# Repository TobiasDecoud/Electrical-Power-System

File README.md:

# Electrical-Power-Subsystem

Necesitamos:
 
  Potencia Requerida: Estimar el consumo de energía promedio y pico de todos los subsistemas del satélite.
  
  Órbita del Satélite: Determinar los períodos de luz solar y eclipse para dimensionar los paneles solares y la capacidad de las baterías.
  
  Vida Útil: Seleccionar componentes que puedan soportar la duración de la misión y los ciclos de carga y descarga.

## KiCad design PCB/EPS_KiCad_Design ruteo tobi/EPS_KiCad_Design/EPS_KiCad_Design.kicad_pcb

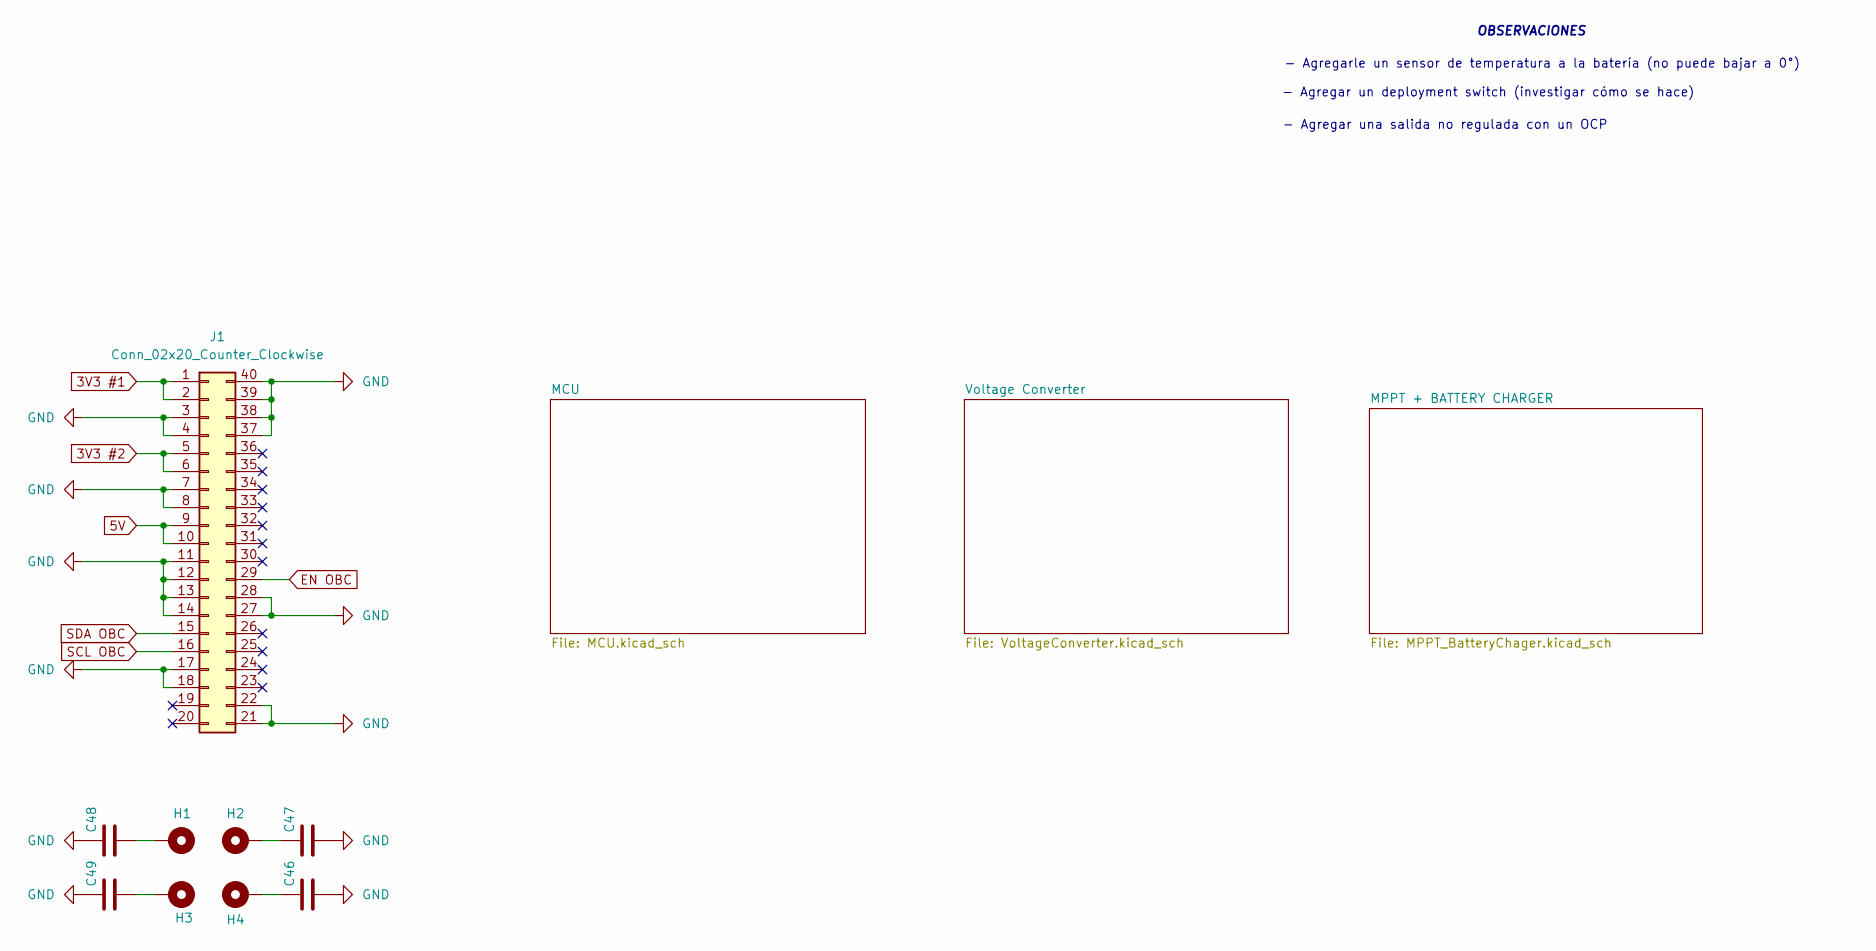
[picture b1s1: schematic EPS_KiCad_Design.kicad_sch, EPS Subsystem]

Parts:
C46, C47, C48, C49: 100nF; C_0805_2012Metric_Pad1.18x1.45mm_HandSolder
H1, H2, H3, H4: MountingHole_Pad; MountingHole_3.2mm_M3_Pad_Via
J1: Conn_02x20_Counter_Clockwise; PinSocket_2x20_P2.54mm_Vertical

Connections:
3V3 #1: J1.1, J1.2; also elsewhere on the board
3V3 #2: J1.5, J1.6; also elsewhere on the board
5V: J1.9, J1.10; also elsewhere on the board
EN OBC: J1.29; also elsewhere on the board
GND: C46.2, C47.2, C48.1, C49.1, J1.3, J1.4, J1.7, J1.8, J1.11, J1.12, J1.13, J1.14, J1.17, J1.18, J1.21, J1.22, J1.27, J1.28, J1.37, J1.38, J1.39, J1.40; also elsewhere on the board
unnamed: C46.1, H4.1
unnamed: C47.1, H2.1
unnamed: C48.2, H1.1
unnamed: C49.2, H3.1
SCL OBC: J1.16; also elsewhere on the board
SDA OBC: J1.15; also elsewhere on the board

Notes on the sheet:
OBSERVACIONES
- Agregar un deployment switch (investigar cómo se hace)
- Agregarle un sensor de temperatura a la batería (no puede bajar a 0°)
- Agregar una salida no regulada con un OCP

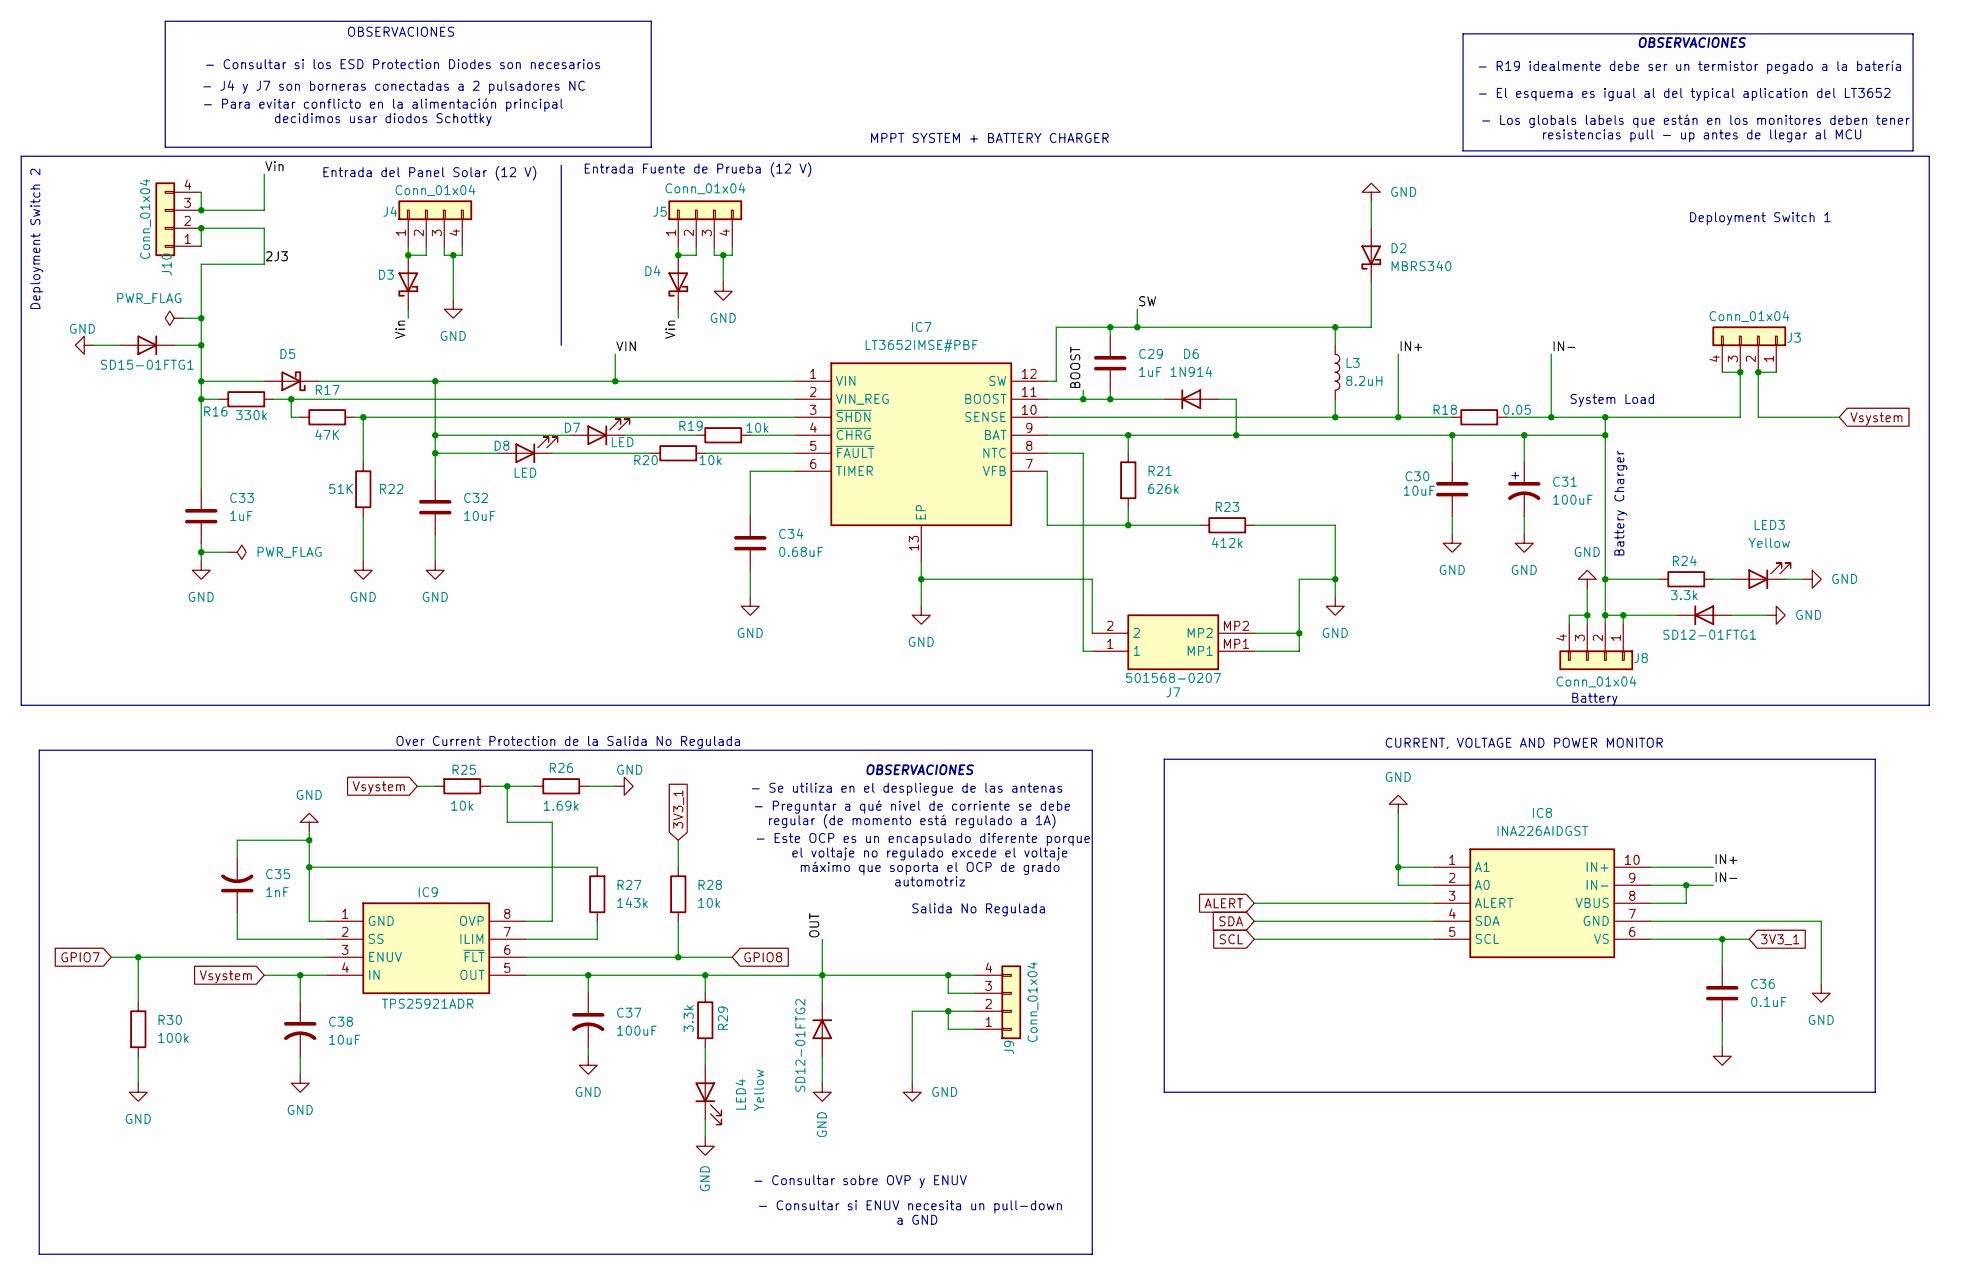
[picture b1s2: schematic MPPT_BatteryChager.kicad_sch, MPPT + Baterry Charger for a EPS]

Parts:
C29, C33: 1uF; C_0805_2012Metric_Pad1.18x1.45mm_HandSolder
C30, C32, C38: 10uF; C_0805_2012Metric_Pad1.18x1.45mm_HandSolder
C31, C37: 100uF; CAPPM7344X310N
C34: 0.68uF; C_0805_2012Metric_Pad1.18x1.45mm_HandSolder
C35: 1nF; C_0805_2012Metric_Pad1.18x1.45mm_HandSolder
C36: 0.1uF; C_0805_2012Metric_Pad1.18x1.45mm_HandSolder
D2, D3, D4, D5: MBRS340; SODFL3517X110N
D6: 1N914; SODFL4725X110N
D7, D8: LED; LED_0805_2012Metric_Pad1.15x1.40mm_HandSolder
IC7: LT3652IMSE#PBF; SOP65P490X110-13N; Mouser Part Number 584-LT3652IMSE#PBF
IC8: INA226AIDGST; SOP50P490X110-10N; Mouser Part Number 595-INA226AIDGST
IC9: TPS25921ADR; SOIC127P600X175-8N; Mouser Part Number 595-TPS25921ADR
J3, J4, J5, J8, J9, J10: Conn_01x04; 62000411722
J7: 501568-0207; 5015680207; Mouser Part Number 538-501568-0207
L3: 8.2uH; INDPM7168X300N
LED3, LED4: Yellow; LED_0805_2012Metric_Pad1.15x1.40mm_HandSolder
R16: 330k; R_0805_2012Metric_Pad1.20x1.40mm_HandSolder
R17: 47K; R_0805_2012Metric_Pad1.20x1.40mm_HandSolder
R18: 0.05; R_0805_2012Metric_Pad1.20x1.40mm_HandSolder
R19, R20, R25, R28: 10k; R_0805_2012Metric_Pad1.20x1.40mm_HandSolder
R21: 626k; R_0805_2012Metric_Pad1.20x1.40mm_HandSolder
R22: 51K; R_0805_2012Metric_Pad1.20x1.40mm_HandSolder
R23: 412k; R_0805_2012Metric_Pad1.20x1.40mm_HandSolder
R24, R29: 3.3k; R_0805_2012Metric_Pad1.20x1.40mm_HandSolder
R26: 1.69k; R_0805_2012Metric_Pad1.20x1.40mm_HandSolder
R27: 143k; R_0805_2012Metric_Pad1.20x1.40mm_HandSolder
R30: 100k; R_0805_2012Metric_Pad1.20x1.40mm_HandSolder
SD12-01FTG1, SD12-01FTG2: SOD2613X114N
SD15-01FTG1: D; SOD2613X114N

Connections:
3V3_1: C36.1, IC8.6 (VS), R28.1; also elsewhere on the board
/MPPT + BATTERY CHARGER/2J3: C33.1, D5.2 (A), J10.1, J10.2, R16.1, SD15-01FTG1.1 (K)
/MPPT + BATTERY CHARGER/BOOST: C29.2, D6.1 (K), IC7.11 (BOOST)
/MPPT + BATTERY CHARGER/IN+: IC7.10 (SENSE), IC8.10 (IN+), L3.2, R18.1
/MPPT + BATTERY CHARGER/IN-: C30.1, C31.1, D6.2 (A), IC7.9 (BAT), IC8.8 (VBUS), IC8.9 (IN-), J3.3, J3.4, J8.1, J8.2, R18.2, R21.1, R24.1, SD12-01FTG1.1 (K)
/MPPT + BATTERY CHARGER/OUT: C37.1, IC9.5 (OUT), J9.3, J9.4, R29.1, SD12-01FTG2.1 (K)
/MPPT + BATTERY CHARGER/SW: C29.1, D2.1 (K), IC7.12 (SW), L3.1
/MPPT + BATTERY CHARGER/VIN: C32.1, D5.1 (K), D7.2 (A), D8.2 (A), IC7.1 (VIN)
/MPPT + BATTERY CHARGER/Vin: D3.1 (K), D4.1 (K), J10.3, J10.4
ALERT: IC8.3 (ALERT); also elsewhere on the board
GND: C30.2, C31.2, C32.2, C33.2, C34.2, C35.2, C36.2, C37.2, C38.2, D2.2 (A), IC7.13 (EP), IC8.1 (A1), IC8.2 (A0), IC8.7 (GND), IC9.1 (GND), J4.3, J4.4, J5.3, J5.4, J7.2, J7.MP1, J7.MP2, J8.3, J8.4, J9.1, J9.2, LED3.1 (K), LED4.1 (K), R22.2, R23.2, R26.2, R27.2, R30.2, SD12-01FTG1.2 (A), SD12-01FTG2.2 (A), SD15-01FTG1.2 (A); also elsewhere on the board
GPIO7: IC9.3 (ENUV), R30.1; also elsewhere on the board
GPIO8: IC9.6 (~FLT), R28.2; also elsewhere on the board
unnamed: D3.2 (A), J4.1, J4.2
unnamed: D4.2 (A), J5.1, J5.2
unnamed: D7.1 (K), R19.1
unnamed: D8.1 (K), R20.1
unnamed: IC7.8 (NTC), J7.1
unnamed: C34.1, IC7.6 (TIMER)
unnamed: IC7.7 (VFB), R21.2, R23.1
unnamed: IC7.2 (VIN_REG), R16.2, R17.1
unnamed: IC7.4 (~CHRG), R19.2
unnamed: IC7.5 (~FAULT), R20.2
unnamed: IC7.3 (~SHDN), R17.2, R22.1
unnamed: IC9.7 (ILIM), R27.1
unnamed: IC9.8 (OVP), R25.1, R26.1
unnamed: C35.1, IC9.2 (SS)
unnamed: LED3.2 (A), R24.2
unnamed: LED4.2 (A), R29.2
SCL: IC8.5 (SCL); also elsewhere on the board
SDA: IC8.4 (SDA); also elsewhere on the board
Vsystem: C38.1, IC9.4 (IN), J3.1, J3.2, R25.2; also elsewhere on the board

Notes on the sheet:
CURRENT, VOLTAGE AND POWER MONITOR
- Se utiliza en el despliegue de las antenas
System Load
OBSERVACIONES
Entrada del Panel Solar (12 V)
- Los globals labels que están en los monitores deben tener resistencias pull - up antes de llegar al MCU
- Para evitar conflicto en la alimentación principal decidimos usar diodos Schottky
Battery Charger
- Este OCP es un encapsulado diferente porque el voltaje no regulado excede el voltaje máximo que soporta el OCP de grado automotriz
- El esquema es igual al del typical aplication del LT3652
Over Current Protection de la Salida No Regulada
- Consultar si ENUV necesita un pull-down a GND
Deployment Switch 1
Entrada Fuente de Prueba (12 V)
Deployment Switch 2
- R19 idealmente debe ser un termistor pegado a la batería
- J4 y J7 son borneras conectadas a 2 pulsadores NC
- Consultar si los ESD Protection Diodes son necesarios
- Consultar sobre OVP y ENUV
Salida No Regulada
- Preguntar a qué nivel de corriente se debe regular (de momento está regulado a 1A)
Battery
MPPT SYSTEM + BATTERY CHARGER

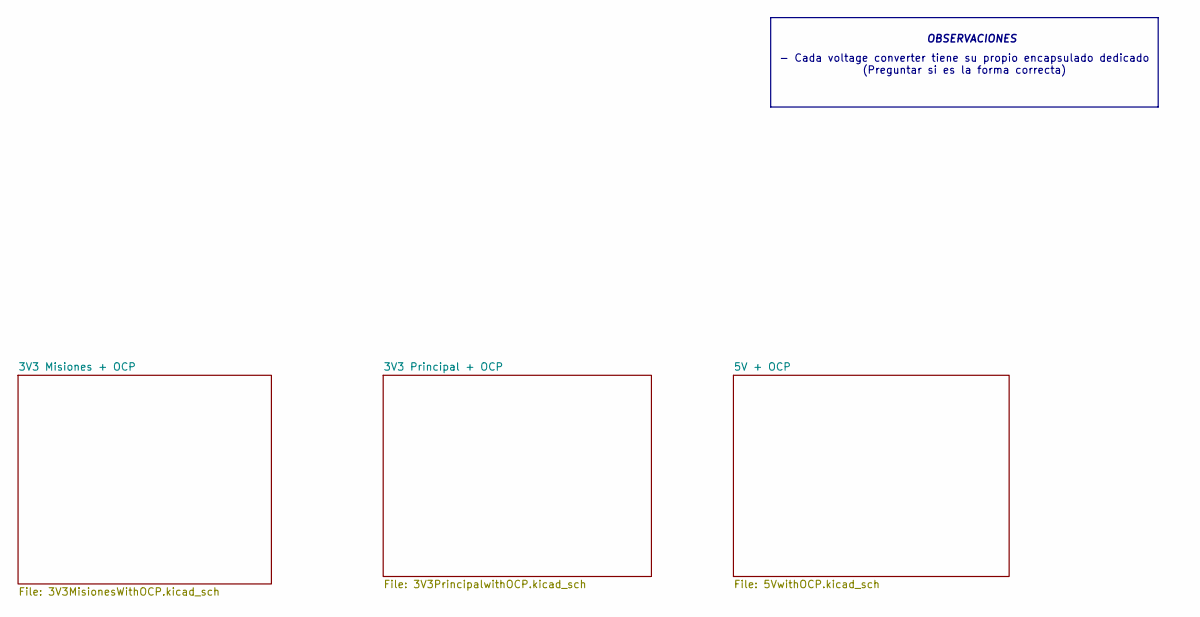
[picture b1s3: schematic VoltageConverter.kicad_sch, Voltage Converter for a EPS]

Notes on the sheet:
- Cada voltage converter tiene su propio encapsulado dedicado (Preguntar si es la forma correcta)
OBSERVACIONES

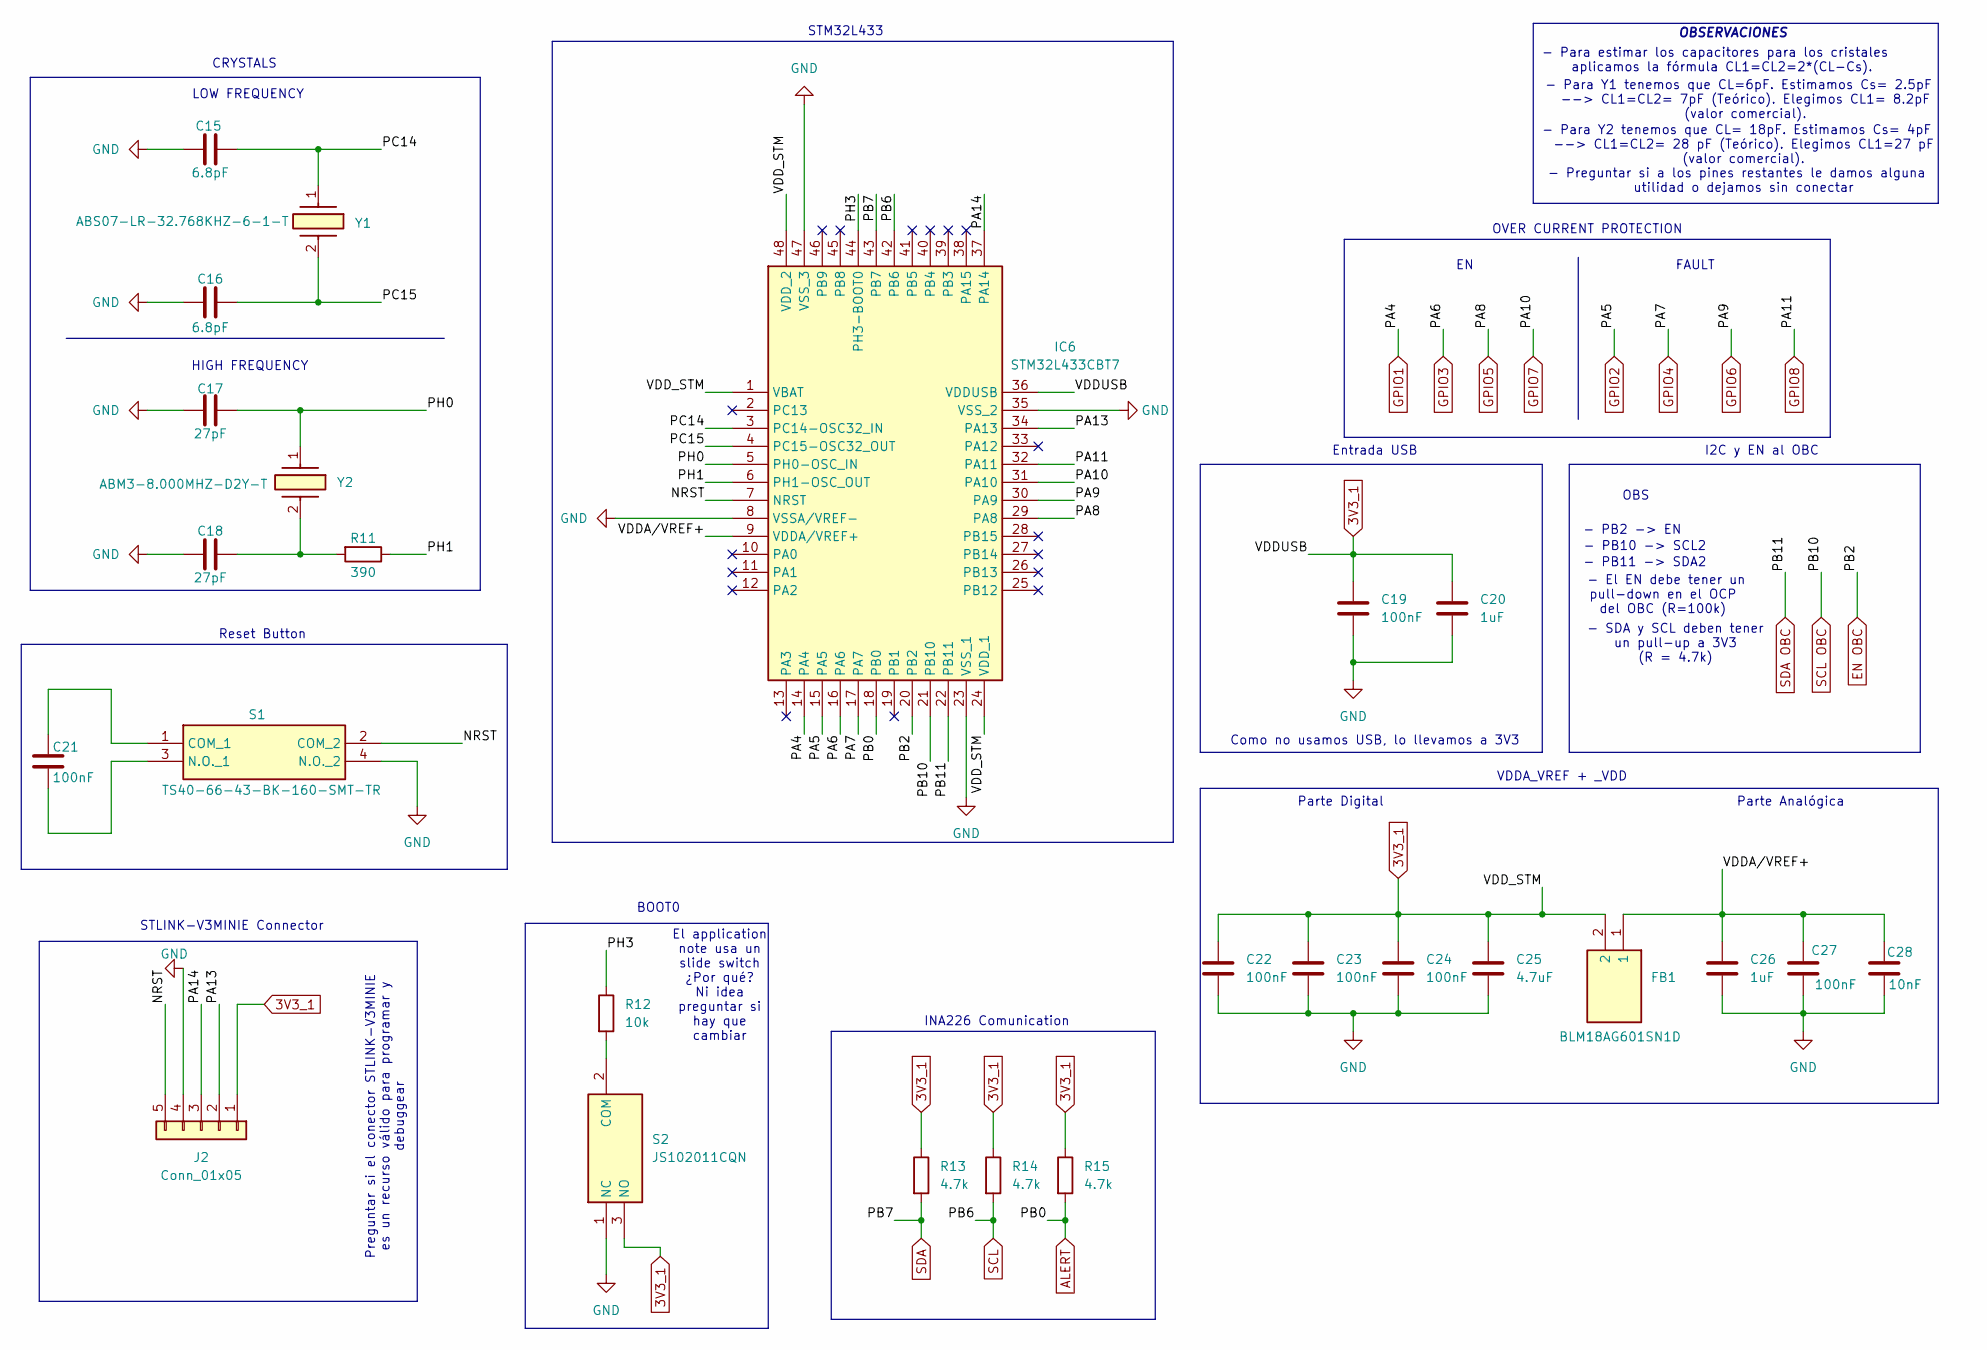
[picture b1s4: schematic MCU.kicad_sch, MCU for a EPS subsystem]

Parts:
C15, C16: 6.8pF; C_0805_2012Metric_Pad1.18x1.45mm_HandSolder
C17, C18: 27pF; C_0805_2012Metric_Pad1.18x1.45mm_HandSolder
C19, C21, C22, C23, C24, C27: 100nF; C_0805_2012Metric_Pad1.18x1.45mm_HandSolder
C20, C26: 1uF; C_0805_2012Metric_Pad1.18x1.45mm_HandSolder
C25: 4.7uF; C_0805_2012Metric_Pad1.18x1.45mm_HandSolder
C28: 10nF; C_0805_2012Metric_Pad1.18x1.45mm_HandSolder
FB1: BLM18AG601SN1D; BLM18SP221SN1B; Mouser Part Number 81-BLM11A601S
IC6: STM32L433CBT7; QFP50P900X900X160-48N; Mouser Part Number 511-STM32L433CBT7
J2: Conn_01x05; TSM10501LSV
R11: 390; R_0805_2012Metric_Pad1.20x1.40mm_HandSolder
R12: 10k; R_0805_2012Metric_Pad1.20x1.40mm_HandSolder
R13, R14, R15: 4.7k; R_0805_2012Metric_Pad1.20x1.40mm_HandSolder
S1: TS40-66-43-BK-160-SMT-TR; TS406643BK160SMTTR; Manufacturer_Part_Number TS40-66-43-BK-160-SMT-TR
S2: JS102011CQN; Mouser Part Number 611-JS102011CQN
Y1: ABS07-LR-32.768KHZ-6-1-T; ABS07LR32768kHz61T; Mouser Part Number 815-ABS07LR32.76-61T
Y2: ABM3-8.000MHZ-D2Y-T; ABM3; Mouser Part Number 815-ABM3-8-D2Y-T

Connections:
3V3_1: C19.1, C20.1, C22.1, C23.1, C24.1, C25.1, FB1.2, IC6.1 (VBAT), IC6.24 (VDD_1), IC6.36 (VDDUSB), IC6.48 (VDD_2), J2.1, R13.1, R14.1, R15.1, S2.3 (NO); also elsewhere on the board
/MCU/NRST: IC6.7 (NRST), J2.5, S1.2 (COM_2)
/MCU/PA13: IC6.34 (PA13), J2.2
/MCU/PA14: IC6.37 (PA14), J2.3
/MCU/PC14: C15.2, IC6.3 (PC14-OSC32_IN), Y1.1
/MCU/PC15: C16.2, IC6.4 (PC15-OSC32_OUT), Y1.2
/MCU/PH0: C17.1, IC6.5 (PH0-OSC_IN), Y2.1
/MCU/PH1: IC6.6 (PH1-OSC_OUT), R11.1
/MCU/PH3: IC6.44 (PH3-BOOT0), R12.1
/MCU/VDDA/VREF+: C26.1, C27.1, C28.1, FB1.1, IC6.9 (VDDA/VREF+)
ALERT: IC6.18 (PB0), R15.2; also elsewhere on the board
EN OBC: IC6.20 (PB2); also elsewhere on the board
GND: C15.1, C16.1, C17.2, C18.2, C19.2, C20.2, C22.2, C23.2, C24.2, C25.2, C26.2, C27.2, C28.2, IC6.8 (VSSA/VREF-), IC6.23 (VSS_1), IC6.35 (VSS_2), IC6.47 (VSS_3), J2.4, S1.4 (N.O._2), S2.1 (NC); also elsewhere on the board
GPIO1: IC6.14 (PA4); also elsewhere on the board
GPIO2: IC6.15 (PA5); also elsewhere on the board
GPIO3: IC6.16 (PA6); also elsewhere on the board
GPIO4: IC6.17 (PA7); also elsewhere on the board
GPIO5: IC6.29 (PA8); also elsewhere on the board
GPIO6: IC6.30 (PA9); also elsewhere on the board
GPIO7: IC6.31 (PA10); also elsewhere on the board
GPIO8: IC6.32 (PA11); also elsewhere on the board
unnamed: C18.1, R11.2, Y2.2
unnamed: C21.1, S1.1 (COM_1)
unnamed: C21.2, S1.3 (N.O._1)
unnamed: R12.2, S2.2 (COM)
SCL: IC6.42 (PB6), R14.2; also elsewhere on the board
SCL OBC: IC6.21 (PB10); also elsewhere on the board
SDA: IC6.43 (PB7), R13.2; also elsewhere on the board
SDA OBC: IC6.22 (PB11); also elsewhere on the board

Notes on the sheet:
BOOT0
- SDA y SCL deben tener un pull-up a 3V3 (R = 4.7k)
OBSERVACIONES
LOW FREQUENCY
- PB2 -> EN
- PB10 -> SCL2
OVER CURRENT PROTECTION
- El EN debe tener un pull-down en el OCP del OBC (R=100k)
Entrada USB
- Para Y2 tenemos que CL= 18pF. Estimamos Cs= 4pF --> CL1=CL2= 28 pF (Teórico). Elegimos CL1=27 pF (valor comercial).
- PB11 -> SDA2
INA226 Comunication
- Preguntar si a los pines restantes le damos alguna utilidad o dejamos sin conectar
Parte Digital
Preguntar si el conector STLINK-V3MINIE es un recurso válido para programar y debuggear
STLINK-V3MINIE Connector
OBS
Reset Button
I2C y EN al OBC
Parte Analógica
FAULT
Como no usamos USB, lo llevamos a 3V3
VDDA_VREF + _VDD
- Para Y1 tenemos que CL=6pF. Estimamos Cs= 2.5pF --> CL1=CL2= 7pF (Teórico). Elegimos CL1= 8.2pF (valor comercial).
El application note usa un slide switch ¿Por qué? Ni idea preguntar si hay que cambiar
CRYSTALS
HIGH FREQUENCY
STM32L433
- Para estimar los capacitores para los cristales aplicamos la fórmula CL1=CL2=2*(CL-Cs).

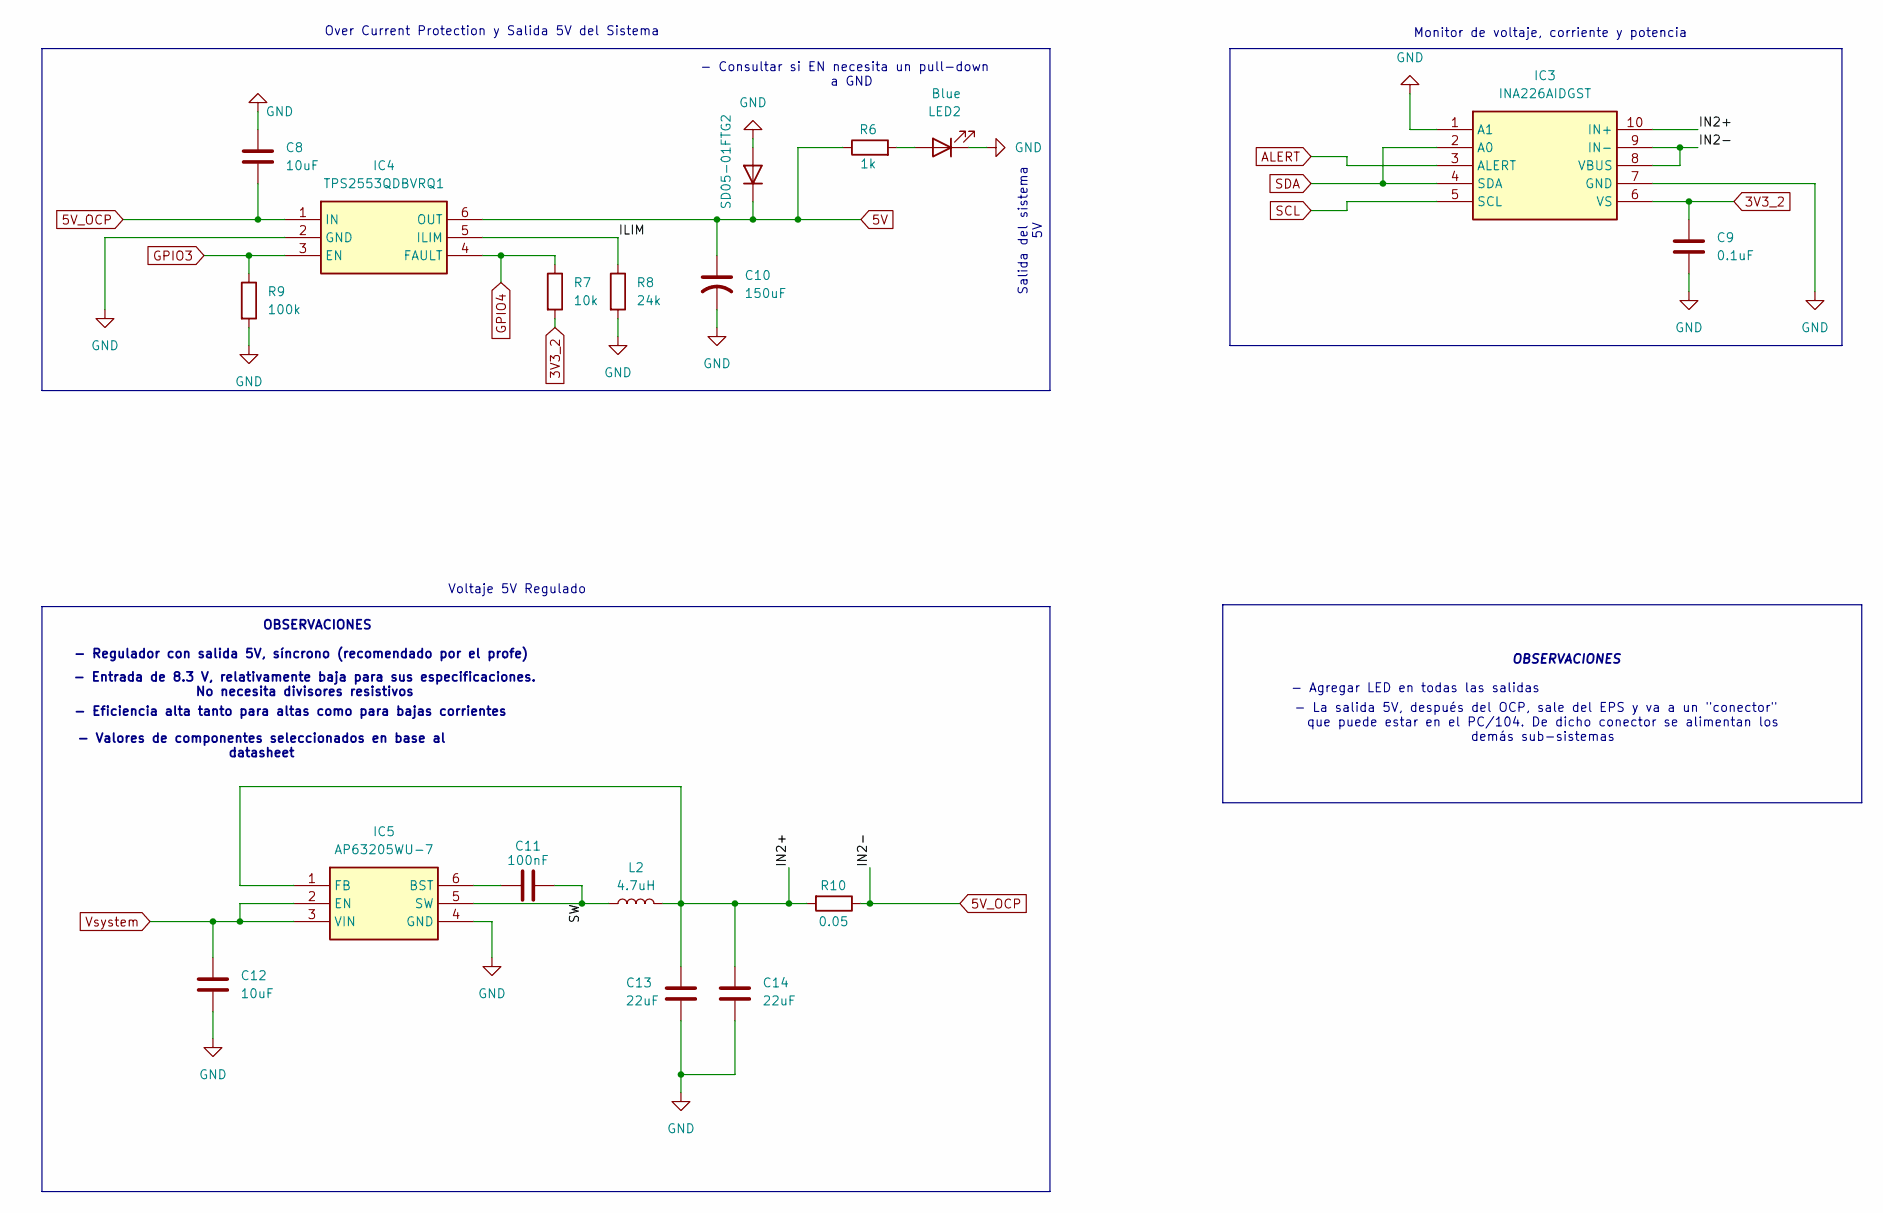
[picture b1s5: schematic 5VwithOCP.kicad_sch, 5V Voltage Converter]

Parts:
C8, C12: 10uF; C_0805_2012Metric_Pad1.18x1.45mm_HandSolder
C9: 0.1uF; C_0805_2012Metric_Pad1.18x1.45mm_HandSolder
C10: 150uF; CAPPM3528X210N
C11: 100nF; C_0805_2012Metric_Pad1.18x1.45mm_HandSolder
C13, C14: 22uF; C_0805_2012Metric_Pad1.18x1.45mm_HandSolder
IC3: INA226AIDGST; SOP50P490X110-10N; Mouser Part Number 595-INA226AIDGST
IC4: TPS2553QDBVRQ1; SOT95P280X145-6N; Mouser Part Number 595-TPS2553QDBVRQ1
IC5: AP63205WU-7; AP63205WU7; Mouser Part Number 621-AP63205WU-7
L2: 4.7uH; INDPM4441X200N
LED2: Blue; LED_0805_2012Metric_Pad1.15x1.40mm_HandSolder
R6: 1k; R_0805_2012Metric_Pad1.20x1.40mm_HandSolder
R7: 10k; R_0805_2012Metric_Pad1.20x1.40mm_HandSolder
R8: 24k; R_0805_2012Metric_Pad1.20x1.40mm_HandSolder
R9: 100k; R_0805_2012Metric_Pad1.20x1.40mm_HandSolder
R10: 0.05; R_0805_2012Metric_Pad1.20x1.40mm_HandSolder
SD05-01FTG2: D; SODFL3718X140N

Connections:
3V3_2: C9.1, IC3.6 (VS), R7.2; also elsewhere on the board
5V: C10.1, IC4.6 (OUT), R6.1, SD05-01FTG2.1 (K); also elsewhere on the board
5V_OCP: C8.2, IC3.8 (VBUS), IC3.9 (IN-), IC4.1 (IN), R10.1
/Voltage Converter/5V + OCP/ILIM: IC4.5 (ILIM), R8.1
/Voltage Converter/5V + OCP/IN2+: C13.1, C14.1, IC3.10 (IN+), IC5.1 (FB), L2.2, R10.2
/Voltage Converter/5V + OCP/SW: C11.2, IC5.5 (SW), L2.1
ALERT: IC3.3 (ALERT); also elsewhere on the board
GND: C8.1, C9.2, C10.2, C12.2, C13.2, C14.2, IC3.1 (A1), IC3.7 (GND), IC4.2 (GND), IC5.4 (GND), LED2.1 (K), R8.2, R9.2, SD05-01FTG2.2 (A); also elsewhere on the board
GPIO3: IC4.3 (EN), R9.1; also elsewhere on the board
GPIO4: IC4.4 (FAULT), R7.1; also elsewhere on the board
unnamed: C11.1, IC5.6 (BST)
unnamed: LED2.2 (A), R6.2
SCL: IC3.5 (SCL); also elsewhere on the board
SDA: IC3.2 (A0), IC3.4 (SDA); also elsewhere on the board
Vsystem: C12.1, IC5.2 (EN), IC5.3 (VIN); also elsewhere on the board

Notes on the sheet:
- Consultar si EN necesita un pull-down a GND
Voltaje 5V Regulado
OBSERVACIONES
- Eficiencia alta tanto para altas como para bajas corrientes
- Agregar LED en todas las salidas
- Entrada de 8.3 V, relativamente baja para sus especificaciones. No necesita divisores resistivos
Salida del sistema 5V
- La salida 5V, después del OCP, sale del EPS y va a un "conector" que puede estar en el PC/104. De dicho conector se alimentan los demás sub-sistemas
- Valores de componentes seleccionados en base al datasheet
Over Current Protection y Salida 5V del Sistema
Monitor de voltaje, corriente y potencia
- Regulador con salida 5V, síncrono (recomendado por el profe)

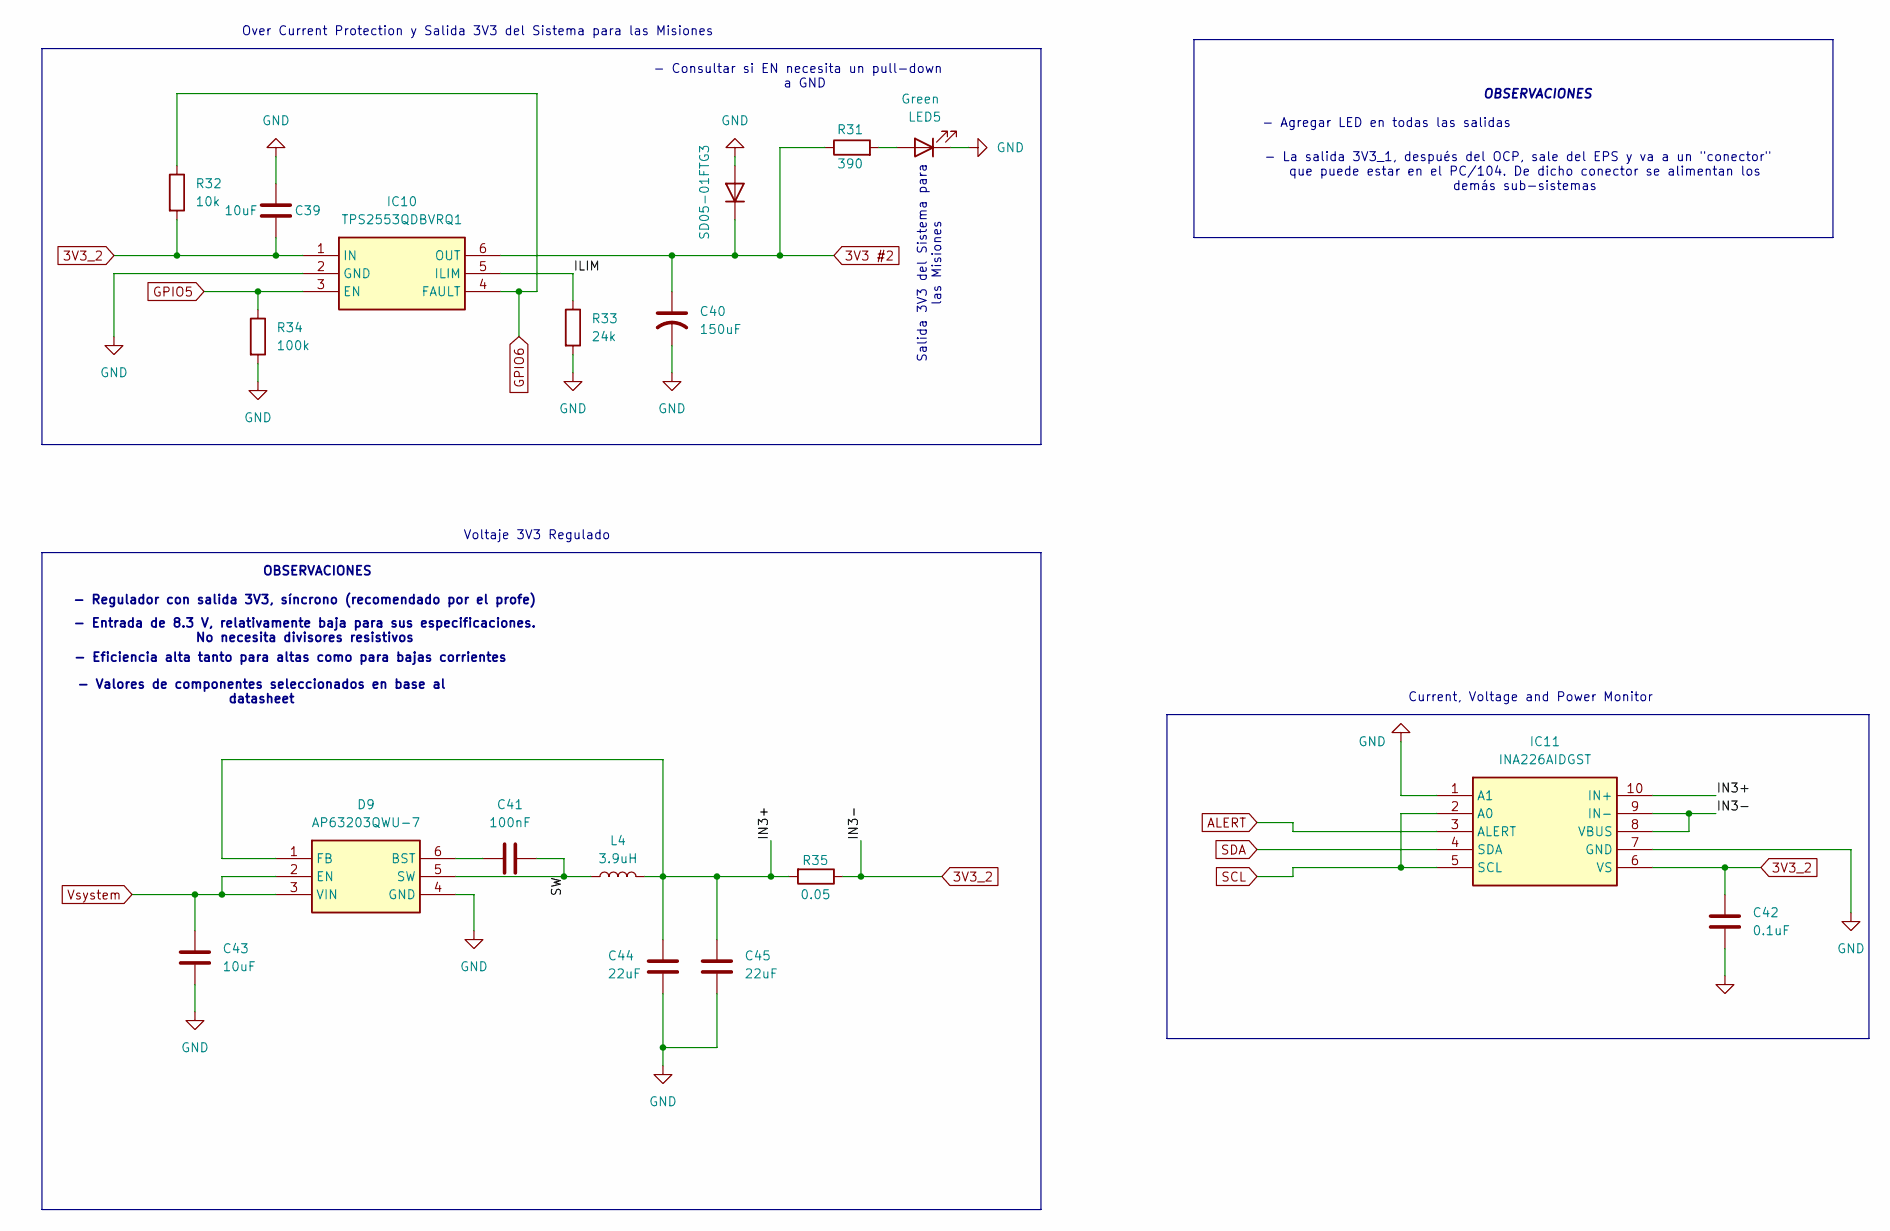
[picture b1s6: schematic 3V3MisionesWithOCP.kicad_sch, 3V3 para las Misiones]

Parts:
C39, C43: 10uF; C_0805_2012Metric_Pad1.18x1.45mm_HandSolder
C40: 150uF; CAPPM3528X210N
C41: 100nF; C_0805_2012Metric_Pad1.18x1.45mm_HandSolder
C42: 0.1uF; C_0805_2012Metric_Pad1.18x1.45mm_HandSolder
C44, C45: 22uF; C_0805_2012Metric_Pad1.18x1.45mm_HandSolder
D9: AP63203QWU-7; SOT95P280X100-6N; Mouser Part Number 621-AP63203QWU-7
IC10: TPS2553QDBVRQ1; SOT95P280X145-6N; Mouser Part Number 595-TPS2553QDBVRQ1
IC11: INA226AIDGST; SOP50P490X110-10N; Mouser Part Number 595-INA226AIDGST
L4: 3.9uH; ASPI0628150MT1
LED5: Green; LED_0805_2012Metric_Pad1.15x1.40mm_HandSolder
R31: 390; R_0805_2012Metric_Pad1.20x1.40mm_HandSolder
R32: 10k; R_0805_2012Metric_Pad1.20x1.40mm_HandSolder
R33: 24k; R_0805_2012Metric_Pad1.20x1.40mm_HandSolder
R34: 100k; R_0805_2012Metric_Pad1.20x1.40mm_HandSolder
R35: 0.05; R_0805_2012Metric_Pad1.20x1.40mm_HandSolder
SD05-01FTG3: D; SOD2613X114N

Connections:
3V3 #2: C40.1, IC10.6 (OUT), R31.1, SD05-01FTG3.1 (K); also elsewhere on the board
3V3_2: C39.1, C42.1, IC10.1 (IN), IC11.6 (VS), IC11.8 (VBUS), IC11.9 (IN-), R32.2, R35.1; also elsewhere on the board
/Voltage Converter/3V3 Misiones + OCP/ILIM: IC10.5 (ILIM), R33.1
/Voltage Converter/3V3 Misiones + OCP/IN3+: C44.1, C45.1, D9.1 (FB), IC11.10 (IN+), L4.2, R35.2
/Voltage Converter/3V3 Misiones + OCP/SW: C41.2, D9.5 (SW), L4.1
ALERT: IC11.3 (ALERT); also elsewhere on the board
GND: C39.2, C40.2, C42.2, C43.2, C44.2, C45.2, D9.4 (GND), IC10.2 (GND), IC11.1 (A1), IC11.7 (GND), LED5.1 (K), R33.2, R34.2, SD05-01FTG3.2 (A); also elsewhere on the board
GPIO5: IC10.3 (EN), R34.1; also elsewhere on the board
GPIO6: IC10.4 (FAULT), R32.1; also elsewhere on the board
unnamed: C41.1, D9.6 (BST)
unnamed: LED5.2 (A), R31.2
SCL: IC11.2 (A0), IC11.5 (SCL); also elsewhere on the board
SDA: IC11.4 (SDA); also elsewhere on the board
Vsystem: C43.1, D9.2 (EN), D9.3 (VIN); also elsewhere on the board

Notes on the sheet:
OBSERVACIONES
- Eficiencia alta tanto para altas como para bajas corrientes
- Entrada de 8.3 V, relativamente baja para sus especificaciones. No necesita divisores resistivos
Voltaje 3V3 Regulado
- Regulador con salida 3V3, síncrono (recomendado por el profe)
- Agregar LED en todas las salidas
Current, Voltage and Power Monitor
- Valores de componentes seleccionados en base al datasheet
Salida 3V3 del Sistema para las Misiones
- Consultar si EN necesita un pull-down a GND
Over Current Protection y Salida 3V3 del Sistema para las Misiones
- La salida 3V3_1, después del OCP, sale del EPS y va a un "conector" que puede estar en el PC/104. De dicho conector se alimentan los demás sub-sistemas
